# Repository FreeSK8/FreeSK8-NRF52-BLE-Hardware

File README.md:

# FreeSK8-NRF52-BLE-Hardware
 KiCAD Design Files for NRF52 BLE Module - Based on Fanstel 840

Documentation WIP

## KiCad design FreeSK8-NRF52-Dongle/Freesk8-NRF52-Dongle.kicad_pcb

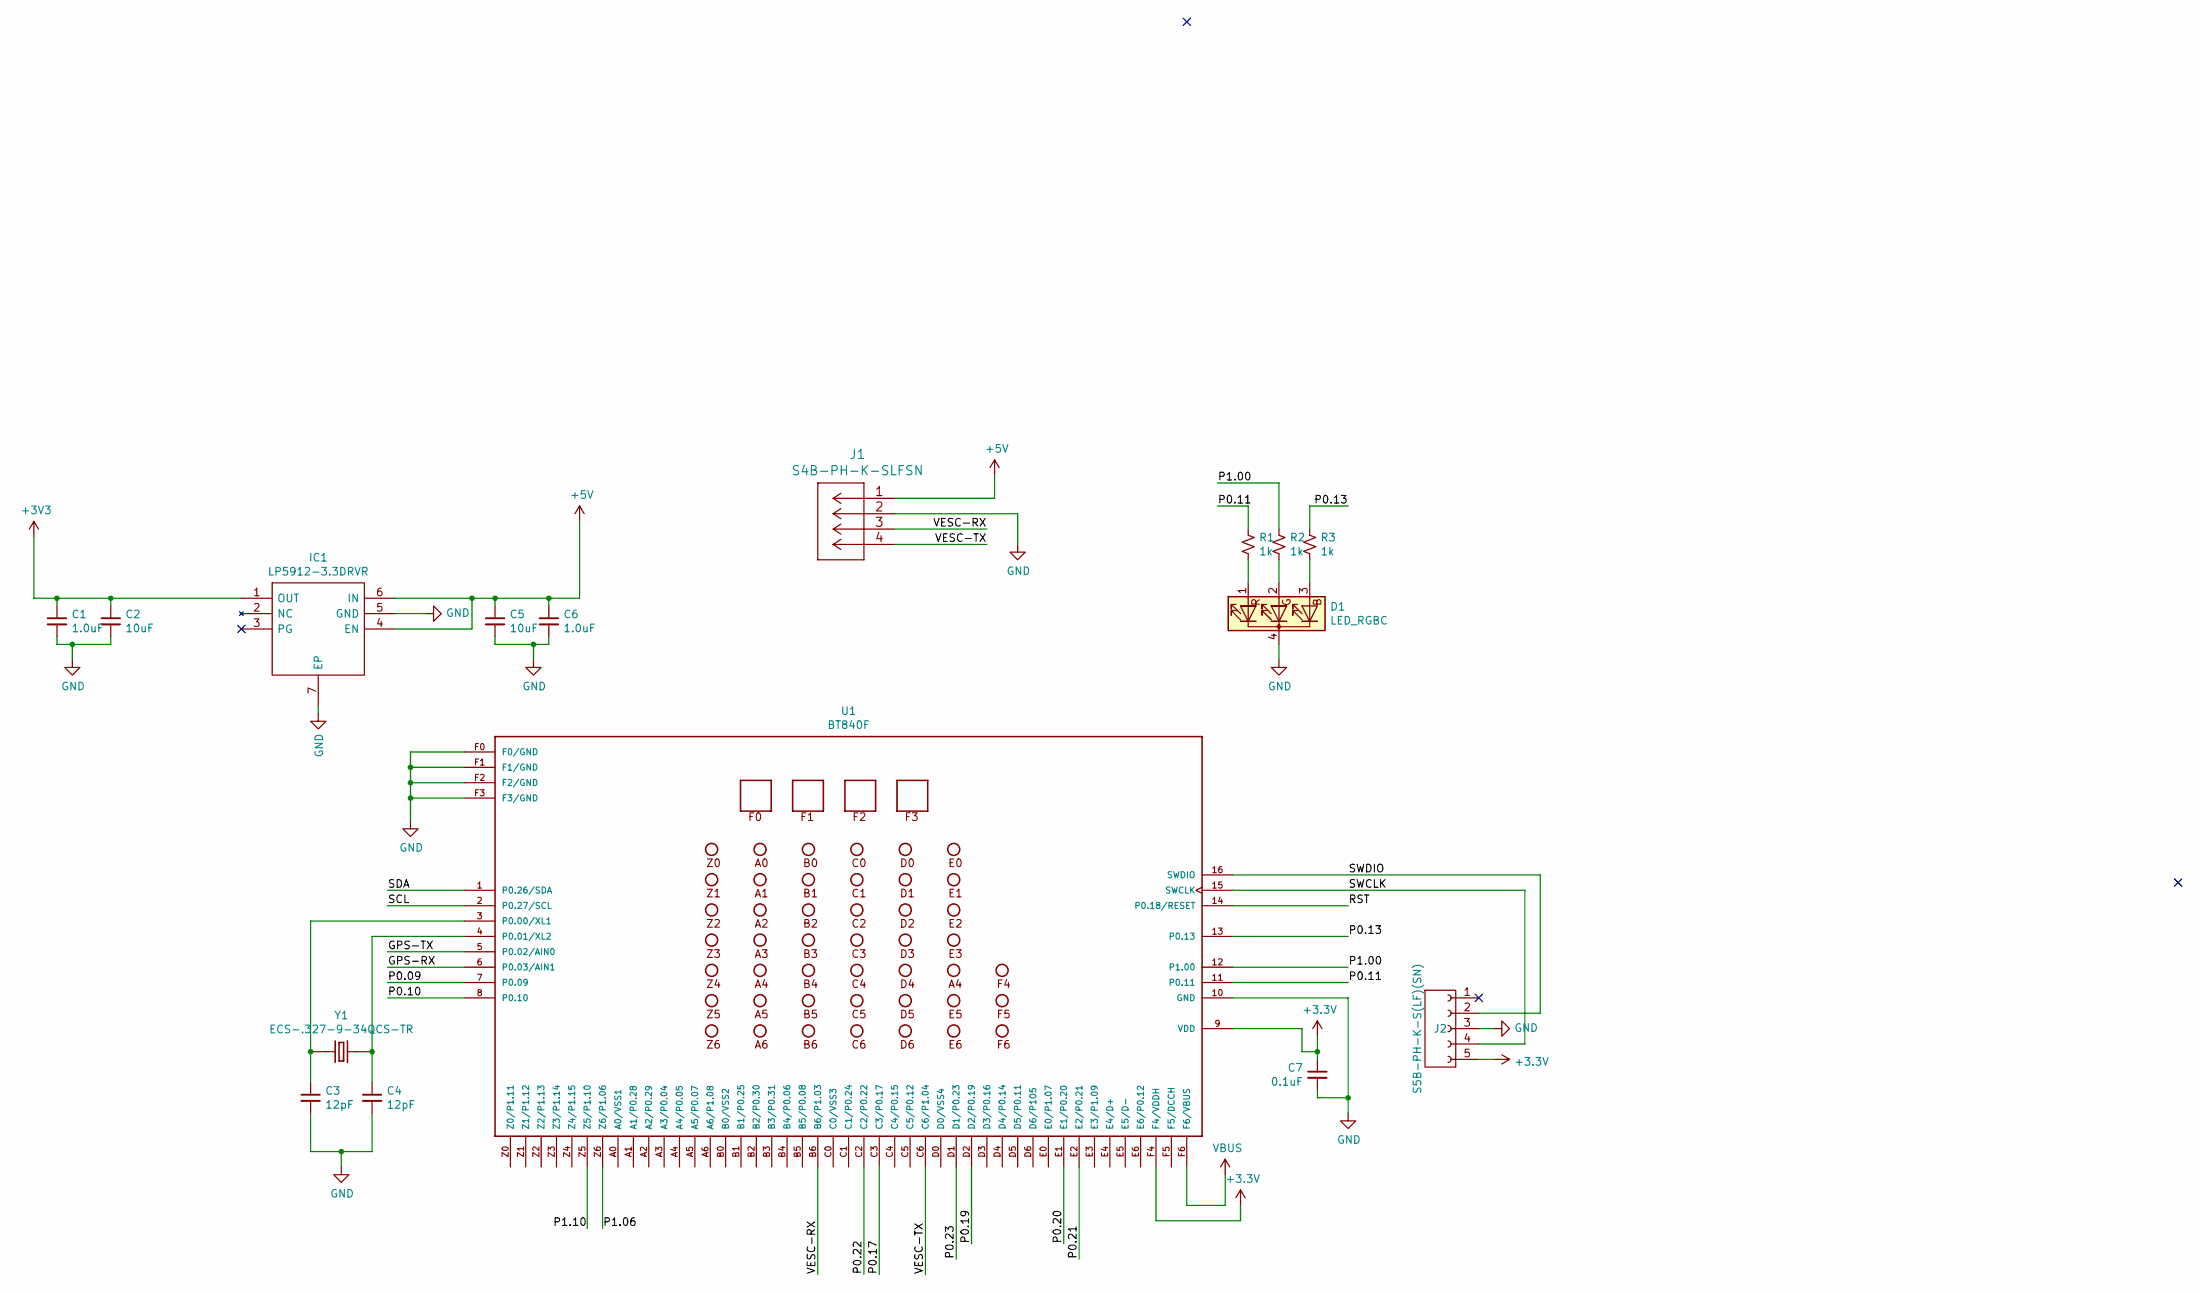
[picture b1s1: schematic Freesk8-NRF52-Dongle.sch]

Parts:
C1, C6: 1.0uF; C_0603_1608Metric
C2, C5: 10uF; C_0805_2012Metric
C3, C4: 12pF; C_0603_1608Metric
C7: 0.1uF; C_0603_1608Metric
D1: LED_RGBC; APTF1616SEEZGQBDC
IC1: LP5912-3.3DRVR; SON65P200X200X80-7N; Mouser Part Number 595-LP5912-3.3DRVR
J1: S4B-PH-K-SLFSN; JST_PH_S4B-PH-K_1x04_P2.00mm_Horizontal
J2: S5B-PH-K-S(LF)(SN); JST_PH_S5B-PH-K_1x05_P2.00mm_Horizontal
R1, R2, R3: 1k; R_0603_1608Metric
U1: BT840F; XCVR_BT840F
Y1: ECS-.327-9-34QCS-TR; XTAL_ECS-.327-9-34QCS-TR

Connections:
+5V: C5.1, C6.1, IC1.4 (EN), IC1.6 (IN), J1.1
/GPS-RX: U1.6 (P0.03/AIN1)
/GPS-TX: U1.5 (P0.02/AIN0)
/P0.09: U1.7 (P0.09)
/P0.10: U1.8 (P0.10)
/P0.11: R1.1, U1.11 (P0.11)
/P0.13: R3.1, U1.13 (P0.13)
/P0.17: U1.C3 (C3/P0.17)
/P0.19: U1.D2 (D2/P0.19)
/P0.20: U1.E1 (E1/P0.20)
/P0.21: U1.E2 (E2/P0.21)
/P0.22: U1.C2 (C2/P0.22)
/P0.23: U1.D1 (D1/P0.23)
/P1.00: R2.1, U1.12 (P1.00)
/P1.06: U1.Z6 (Z6/P1.06)
/P1.10: U1.Z5 (Z5/P1.10)
/RST: U1.14 (P0.18/RESET)
/SCL: U1.2 (P0.27/SCL)
/SDA: U1.1 (P0.26/SDA)
/SWCLK: J2.4, U1.15 (SWCLK)
/SWDIO: J2.2, U1.16 (SWDIO)
/VESC-RX: J1.3, U1.B6 (B6/P1.03)
/VESC-TX: J1.4, U1.C6 (C6/P1.04)
GND: C1.2, C2.2, C3.2, C4.2, C5.2, C6.2, C7.2, D1.4 (K), IC1.5 (GND), IC1.7 (EP), J1.2, J2.3, U1.10 (GND), U1.F0 (F0/GND), U1.F1 (F1/GND), U1.F2 (F2/GND), U1.F3 (F3/GND)
unnamed: C3.1, U1.3 (P0.00/XL1), Y1.1 (I/O)
unnamed: C4.1, U1.4 (P0.01/XL2), Y1.2 (O/I)
unnamed: D1.1 (RA), R1.2
unnamed: D1.2 (GA), R2.2
unnamed: D1.3 (BA), R3.2
VBUS: U1.F6 (F6/VBUS)

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
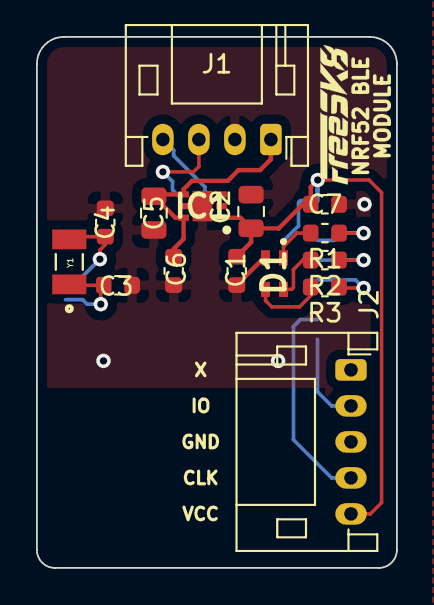
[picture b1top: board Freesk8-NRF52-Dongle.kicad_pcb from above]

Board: 2 copper layers, 20.0 x 29.5 mm, 16 parts (1 on the bottom side), 15 nets.
